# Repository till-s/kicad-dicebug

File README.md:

# The DiceBug

*by Till Straumann, 2023*

## Introduction

This is a simple electronics project that I have created to
teach kids how electronic circuits are "built" -- in a physical
sense. They don't have to understand how it works (6 year olds
have assembled the bug) but just have fun placing the small
components on the board, watching the solder melt in a toaster
oven and walk away with the finished product.

The cute bug features a motion sensor and operates as an "electronic
dice" cycling throught the familiar patterns of pips we know from
traditional dice. The cycling is randomly triggered by hand motion
and happens too fast to control the outcome. When the hand is withdrawn
the bug will show a random facet.

The bug's preferred meal is a CR2032 lithium battery. A small power-switch
is located at the tail end of the animal.

Occasionally, the motion sensor may have to recalibrate itself
(the dice seems to be "stuck" when that happens). Just leave it alone
for several seconds (no touching) and it will come back to life.

Since the battery is exposed don't store the or operate the device
in a conducting bag or box.

## Warning

*Keep (any type of) batteries away from small children. Swallowing
batteries can be life-threatening!*

## Assembly Instructions

### Prerequisites

#### PCB

You need to have the PCB manufactured. There are many companies (mostly
in China) who do this cheaply. I found, however, that most manufacturers
would not offer the red solder mask combined with black ink (silkscreen)
that I liked. Eventually, I came across [elecrow](https://www.elecrow.com)
who would make the PCBs the way I wanted them (slightly more
expensive "premium service").

Make sure to also order a couple of stainless steel stencils
(more than one if you work with groups of kids). PCB manufacturers often
also offer stencils and you save on shipping cost when ordering from a
single source...

#### Parts

The parts can be obtained from the usual electronics distributors
(DigiKey, Mouser, Farnell, ...). These sources also sell solder
paste; I had good results with lead-free low-temperature
paste, Chipquik TS391LT50, which melts around 138degC.

Brass-plated nails, 1.2mm (dia) x 12mm (length), which I found at a DIY shop
make nice legs.

For the actual soldering you'll need a cheap toster oven or a hotplate,
YMMV. There are many instructions available on the internet.

#### IQS211 Capacitive Sensor Programming

Azoteq's IQS211 is very versatile and ideal for this kind of application.
I have regularly found it at Mouser; DigiKey sometimes don't have them.

Note that you need to configure ("burn") the IQS211's OTP options prior
to using it in your application. Unfortunately, this means that you need
the Azoteq CT210 Programmer (also available from distributors) and a
programming socket (e.g., [here](https://github.com/till-s/kicad-sot23-prog.git)).

The configuration value is stated in the schematics.

### Assembly

Nothing special here; I have a bunch of tweezers that I lend to the
kids so that they can work in parallel. Usually a kid's eyesight is
good enough to see the 805 parts perfectly. Adults may need glasses.

Spend some time on the internet if you have never done this; there
are many resources available that teach how to harness SMT.

Obvously, you only install the battery into the holder after soldering
the board.

#### Feet

After assembling and soldering/toasting the board I use a small hammer
and carefully hit the small nails just enough so that they hold on
in the mounting holes. Turn the bug on its feet to verify that it stands
nicely tweaking the feet if necessary. Eventually, you use a conventional
soldering iron and (lead-free) solder to fix the feet permanently.

### Good luck!

### License

This project is licensed under the
[OHL-S open-hardware license](https://ohwr.org/project/cernohl/wikis/Documents/CERN-OHL-version-2);
the artwork was created by my kid Adam and is licensed under
[CC-BY-NC-ND](http://creativecommons.org/licenses/by-nc-nd/4.0/).

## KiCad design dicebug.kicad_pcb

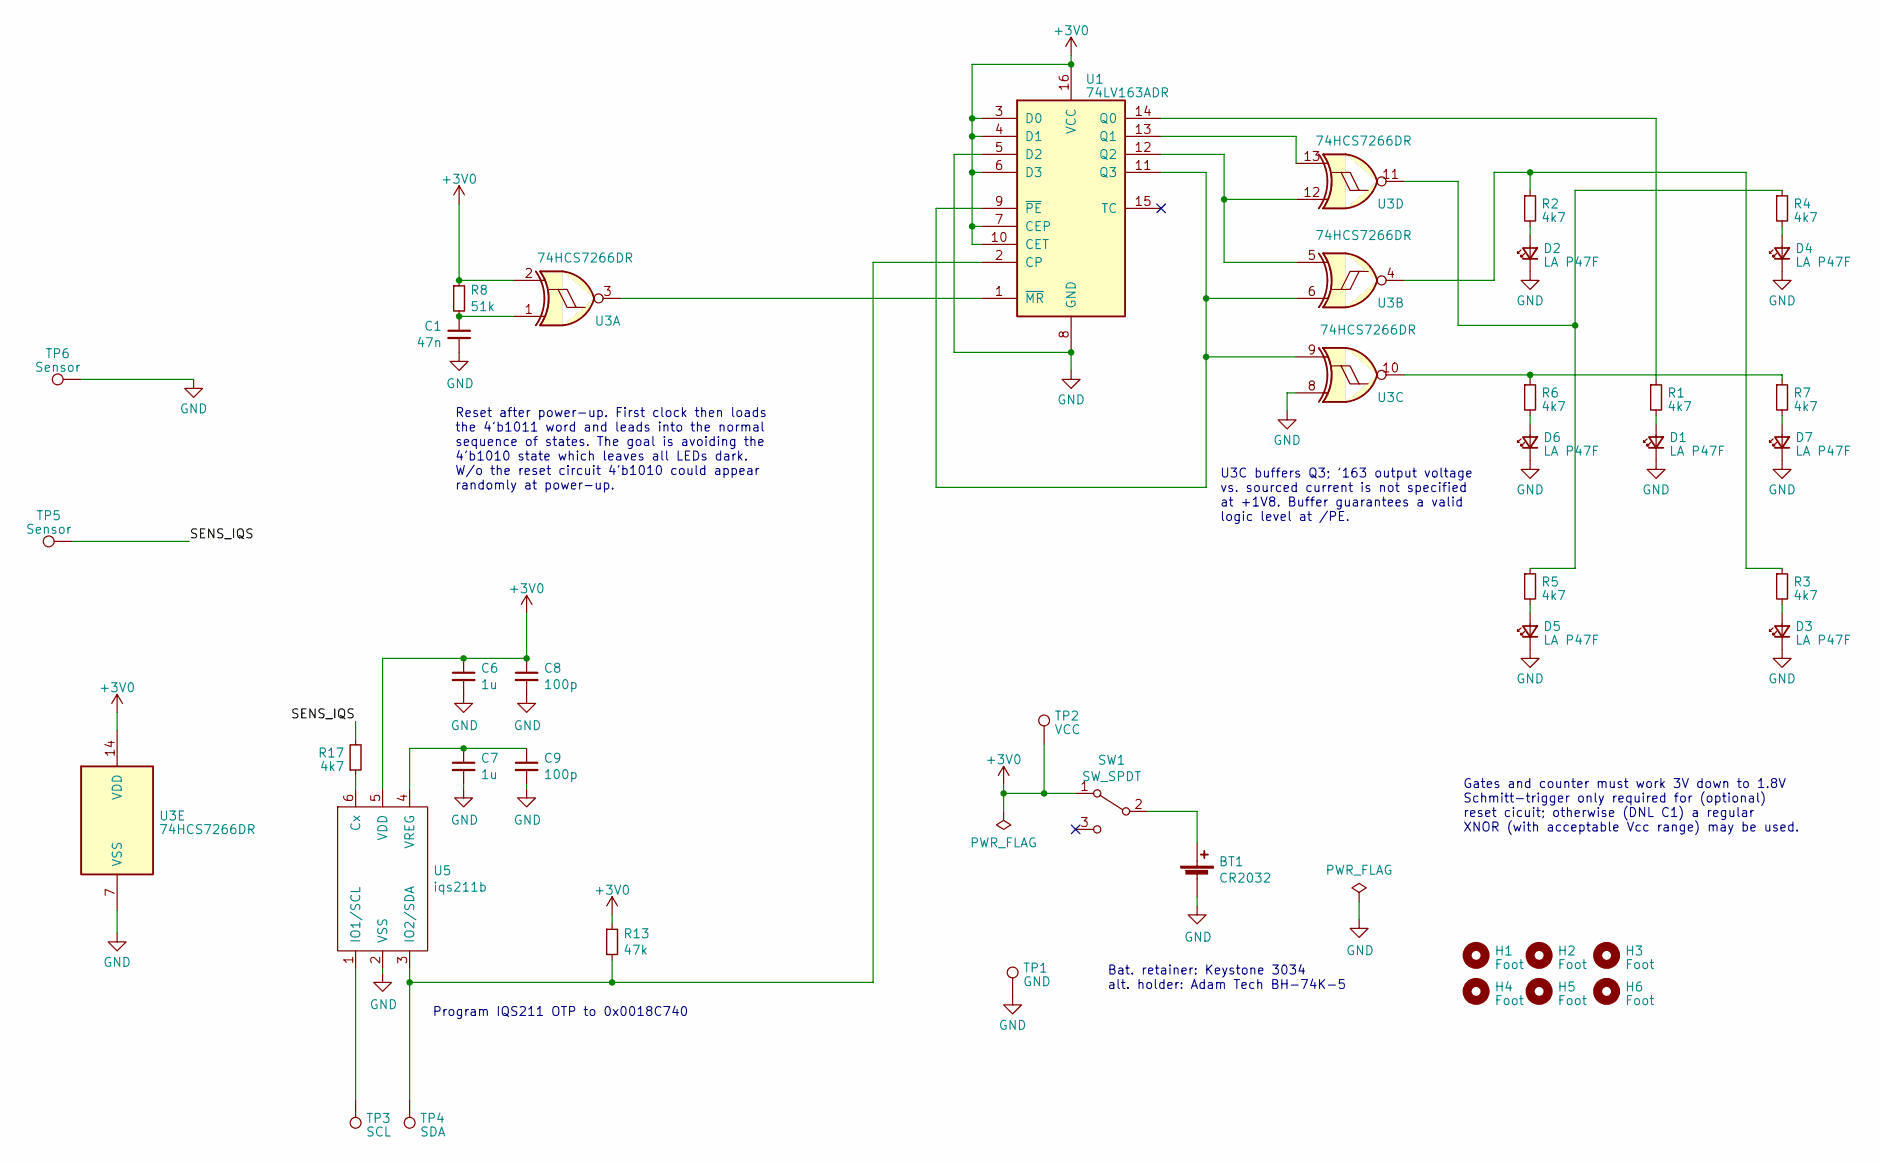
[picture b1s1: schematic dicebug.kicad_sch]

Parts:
BT1: CR2032; bh-3034-74-combined; Part 3034
C1: 47n; C_0805_2012Metric; Part CL21B473KCFNNNF
C6, C7: 1u; C_1206_3216Metric; Part C3216X5R1H105M160AA
C8, C9: 100p; C_0805_2012Metric; Part C0603C101J5GACTU
D1, D2, D3, D4, D5, D6, D7: LA P47F; PointLED_reverse_mount_bigger_pads; Part LA P47F-V2BB-24-3A4B-Z
H1, H2, H3, H4, H5, H6: Foot; foot
R1, R2, R3, R4, R5, R6, R7, R17: 4k7; R_0805_2012Metric
R8: 51k; R_0805_2012Metric
R13: 47k; R_0805_2012Metric
SW1: SW_SPDT; 450404015514; Part 450404015514
TP1: GND; TestPoint_Pad_D2.0mm
TP2: VCC; TestPoint_Pad_D1.0mm
TP3: SCL; TestPoint_Pad_D1.0mm
TP4: SDA; TestPoint_Pad_D1.0mm
TP5, TP6: Sensor; tp_end
U1: 74LV163ADR; SOIC-16_3.9x9.9mm_P1.27mm; Part 74LV163ADR
U3: 74HCS7266DR; SOIC-14_3.9x8.7mm_P1.27mm; Part 74HCS7266DR
U5: iqs211b; SOT-23-6; Part IQS211B

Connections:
+3V0: C6.1, C8.1, R8.1, R13.1, SW1.1 (A), TP2.1, U1.3 (D0), U1.4 (D1), U1.6 (D3), U1.7 (CEP), U1.10 (CET), U1.16 (VCC), U3.2, U3.14 (VDD), U5.5 (VDD)
/SENS_IQS: R17.2, TP5.1
GND: BT1.2 (-), C1.2, C6.2, C7.2, C8.2, C9.2, D1.1 (K), D2.1 (K), D3.1 (K), D4.1 (K), D5.1 (K), D6.1 (K), D7.1 (K), TP1.1, TP6.1, U1.5 (D2), U1.8 (GND), U3.7 (VSS), U3.8, U5.2 (VSS)
unnamed: BT1.1 (+), SW1.2 (B)
unnamed: C1.1, R8.2, U3.1
unnamed: D1.2 (A), R1.2
unnamed: D2.2 (A), R2.2
unnamed: D3.2 (A), R3.2
unnamed: D4.2 (A), R4.2
unnamed: D5.2 (A), R5.2
unnamed: D6.2 (A), R6.2
unnamed: D7.2 (A), R7.2
unnamed: R2.1, R3.1, U3.4
unnamed: R4.1, R5.1, U3.11
unnamed: R6.1, R7.1, U3.10
unnamed: R13.2, TP4.1, U1.2 (CP), U5.3 (IO2/SDA)
unnamed: R1.1, U1.14 (Q0)
unnamed: U1.13 (Q1), U3.13
unnamed: U1.12 (Q2), U3.5, U3.12
unnamed: U1.9 (~PE), U1.11 (Q3), U3.6, U3.9
unnamed: U1.1 (~MR), U3.3
unnamed: R17.1, U5.6 (Cx)
unnamed: TP3.1, U5.1 (IO1/SCL)
unnamed: C7.1, C9.1, U5.4 (VREG)

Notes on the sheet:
Bat. retainer: Keystone 3034 alt. holder: Adam Tech BH-74K-5
Program IQS211 OTP to 0x0018C740
Reset after power-up. First clock then loads the 4'b1011 word and leads into the normal sequence of states. The goal is avoiding the 4'b1010 state which leaves all LEDs dark. W/o the reset circuit 4'b1010 could appear randomly at power-up.
Gates and counter must work 3V down to 1.8V Schmitt-trigger only required for (optional) reset cicuit; otherwise (DNL C1) a regular XNOR (with acceptable Vcc range) may be used.
U3C buffers Q3; '163 output voltage vs. sourced current is not specified at +1V8. Buffer guarantees a valid logic level at /PE.

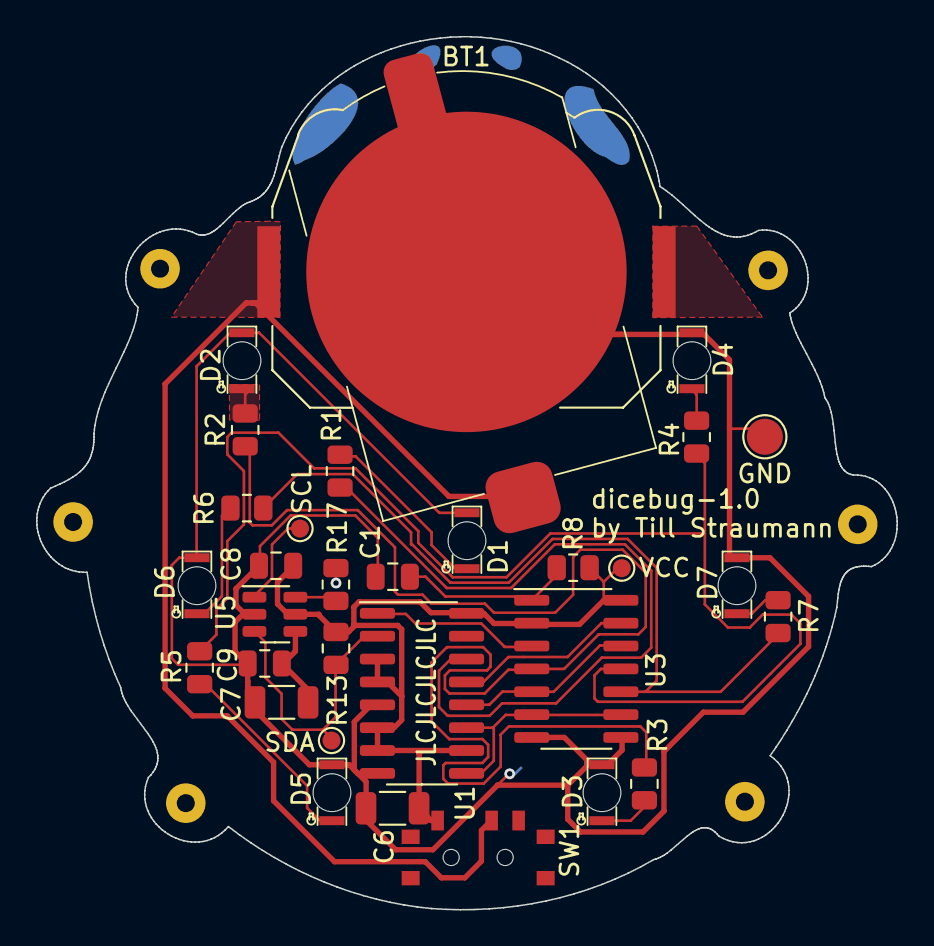
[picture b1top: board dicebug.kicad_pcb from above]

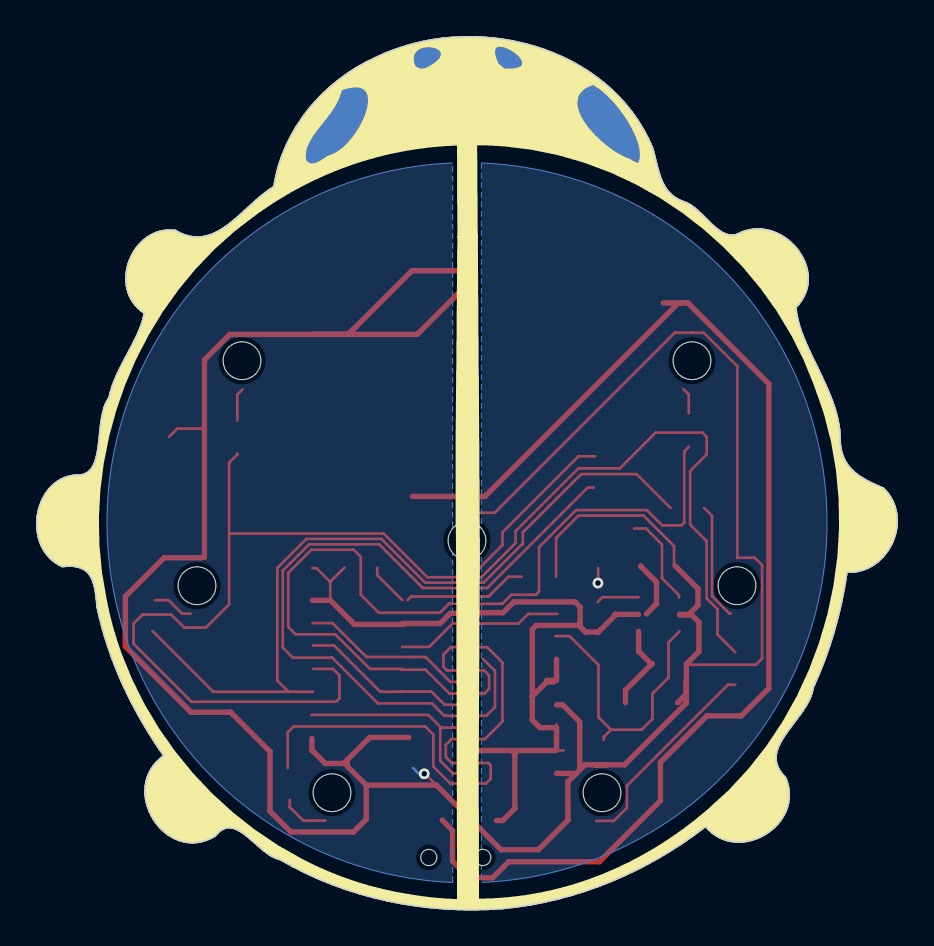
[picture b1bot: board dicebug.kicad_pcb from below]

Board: 2 copper layers, 47.8 x 48.5 mm, 39 parts (2 on the bottom side), 24 nets.

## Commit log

2023-04-13 initialized
2023-04-17 added files to git
2023-05-07 pcb: gerber settings
2023-05-07 removed 1 directory level
2023-05-09 almost finalized with individual LED resistors, though
2023-05-09 Drew schematics for R-array version; works fine.
    No layout; the problem is that there is no reasonably priced
    resistor array in SIOC-16 :-(
2023-05-09 Added README.R-Array
2023-05-09 improved layout (feet area clear)
2023-05-16 WIP: integrating artwork
2023-05-16 mostly done...
2023-05-30 updated part values, numbers/id and manufacturers; added comments
2023-05-30 added missing local footprints; moved art to subdir
2023-05-30 Added title + author info to schematic
2023-05-31 Fixed fab layer
2023-07-03 Removed README.parts (irrelevant)
2023-07-03 Added license for artwork
2023-07-03 art/README.md: removed redundant link
2023-07-03 schematic: added license info
2023-07-03 moved license to OHL
2023-07-03 PCB: removed feet from paste layer.
2023-07-03 added README.md
2023-07-03 added 'belly' picture
2023-07-03 Changed second resistor from 47k to 51k
    The reason for using 51k is simply for easier identification.
    If the resistors have their values printed on the package
    you can distinguish 4k7 vs 51k simply by looking for a 4 vs 5...
2023-07-03 README.md: updated
2023-07-03 README.md: fixed link
2023-07-03 README.md: link still was bad...
2023-07-03 README.md: added license info
2023-07-03 README.md: more link fixes
2023-07-03 Fixing typos
2023-07-03 more typos

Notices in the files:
dicebug.kicad_pcb:
License: OHL-S/CC-BY-NC-ND; no warranty, express or implicit.
